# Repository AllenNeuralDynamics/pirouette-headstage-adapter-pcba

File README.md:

# pirouette-headstage-adapter-pcba

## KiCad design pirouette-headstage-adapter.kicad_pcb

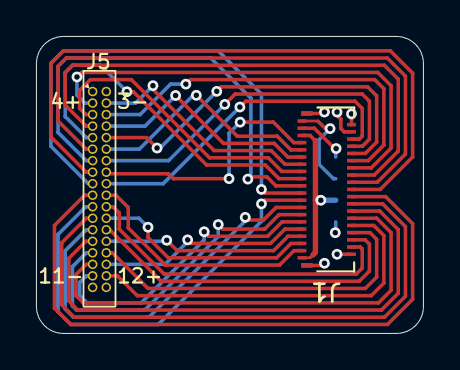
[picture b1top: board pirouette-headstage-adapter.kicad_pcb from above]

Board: 4 copper layers, 21.5 x 16.5 mm, 3 parts (1 on the bottom side), 36 nets.

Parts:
J1: 5040703991; MOLEX_5040703991
J4: Conn_01x04; JST_ACH_BM04B-ACHSS-A-GAN-ETF_1x04-1MP_P1.20mm_Vertical
J5: Conn_02x18_Top_Bottom; Omnetics_NanoStrip_A79023-001_2x36_0.64mm_Vertical

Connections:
/E0+: J1.6, J5.27
/E0-: J1.7, J5.26
/E1+: J1.8, J5.25
/E1-: J1.9, J5.24
/E2+: J1.10, J5.23
/E2-: J1.11, J5.22
/E3+: J1.12, J5.21
/E3-: J1.13, J5.20
/E4+: J1.14, J5.2
/E4-: J1.15, J5.3
/E5+: J1.16, J5.4
/E5-: J1.17, J5.5
/E6+: J1.18, J5.6
/E6-: J1.19, J5.7
/E7+: J1.20, J5.8
/E7-: J1.21, J5.9
/E8+: J1.22, J5.10
/E8-: J1.23, J5.11
/E9+: J1.24, J5.12
/E9-: J1.25, J5.13
/E10+: J1.26, J5.14
/E10-: J1.27, J5.15
/E11+: J1.28, J5.16
/E11-: J1.29, J5.17
/E12+: J1.30, J5.35
/E12-: J1.31, J5.34
/E13+: J1.32, J5.33
/E13-: J1.33 (Pin_31), J5.32
/E14+: J1.34 (Pin_32), J5.31
/E14-: J1.35 (Pin_31), J5.30
/E15+: J1.36 (Pin_32), J5.29
/E15-: J1.37 (Pin_31), J5.28
/NTC_{A}: J1.3, J4.1
/NTC_{B}: J1.1, J4.2
/REF: J1.5, J1.39 (Pin_31), J4.3
GND: J1.2, J1.4, J1.38 (Pin_32), J1.MP1 (MountPin1), J1.MP2 (MountPin2), J4.4, J5.1, J5.18, J5.19, J5.36

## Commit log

2026-06-30 add kicad pcb
